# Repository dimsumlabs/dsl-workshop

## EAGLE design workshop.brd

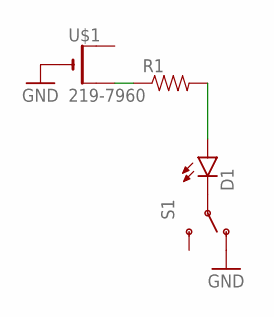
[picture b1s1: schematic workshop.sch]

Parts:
D1: LED10MM
R1: RESISTORKIT; AXIAL-0.3-KIT
S1: SWITCH-SPDT-1; MHS122-1
U$1: 219-7960; CR2032-THRU

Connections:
GND: S1.1 (O), U$1.-
unnamed: D1.A, R1.P$2 (2)
unnamed: D1.C, S1.2
unnamed: R1.P$1 (1), U$1.+2 (+1)

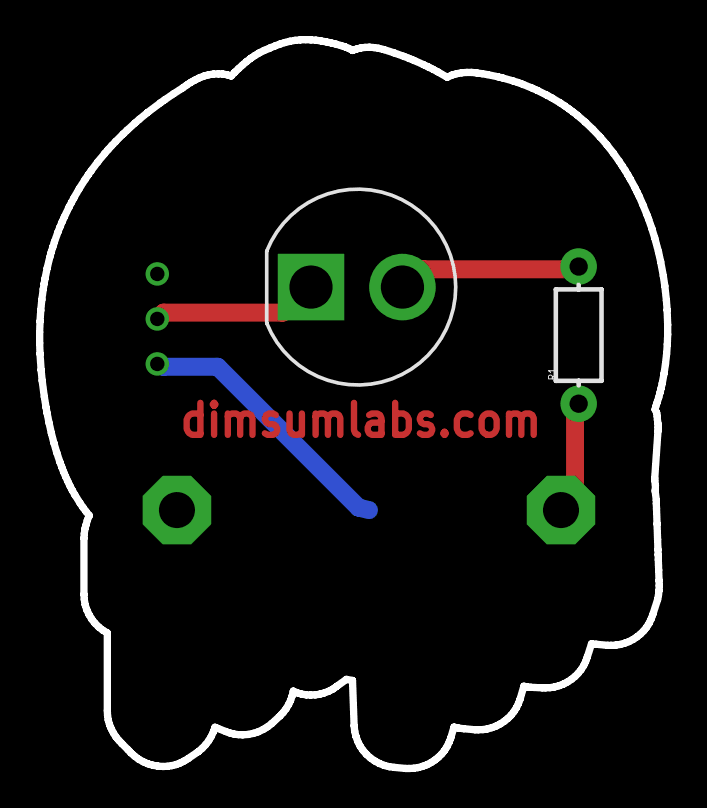
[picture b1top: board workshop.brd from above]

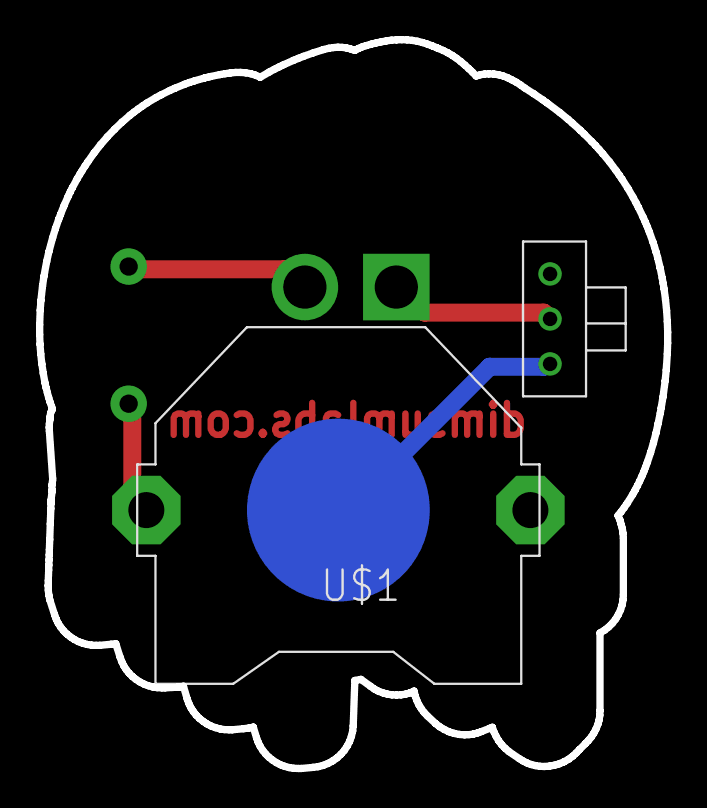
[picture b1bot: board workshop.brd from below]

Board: 2 copper layers, 34.9 x 40.5 mm, 4 parts (2 on the bottom side), 4 nets.

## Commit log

2015-10-24 Initial (drawdio)
2015-10-25 Simpler version with LED and switch
2015-10-25 Fixed switch to MHS122-1 package
2015-10-25 Adding .gitignore for eagle files
2015-10-25 Adding website address
2015-10-25 Ignore .job files
2015-11-01 Changed to simple light with button
2015-11-01 Added screenshot

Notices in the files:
parts and their libraries:
SparkFun-LED: Licensing: Creative Commons ShareAlike 4.0 International - https://creativecommons.org/licenses/by-sa/4.0
